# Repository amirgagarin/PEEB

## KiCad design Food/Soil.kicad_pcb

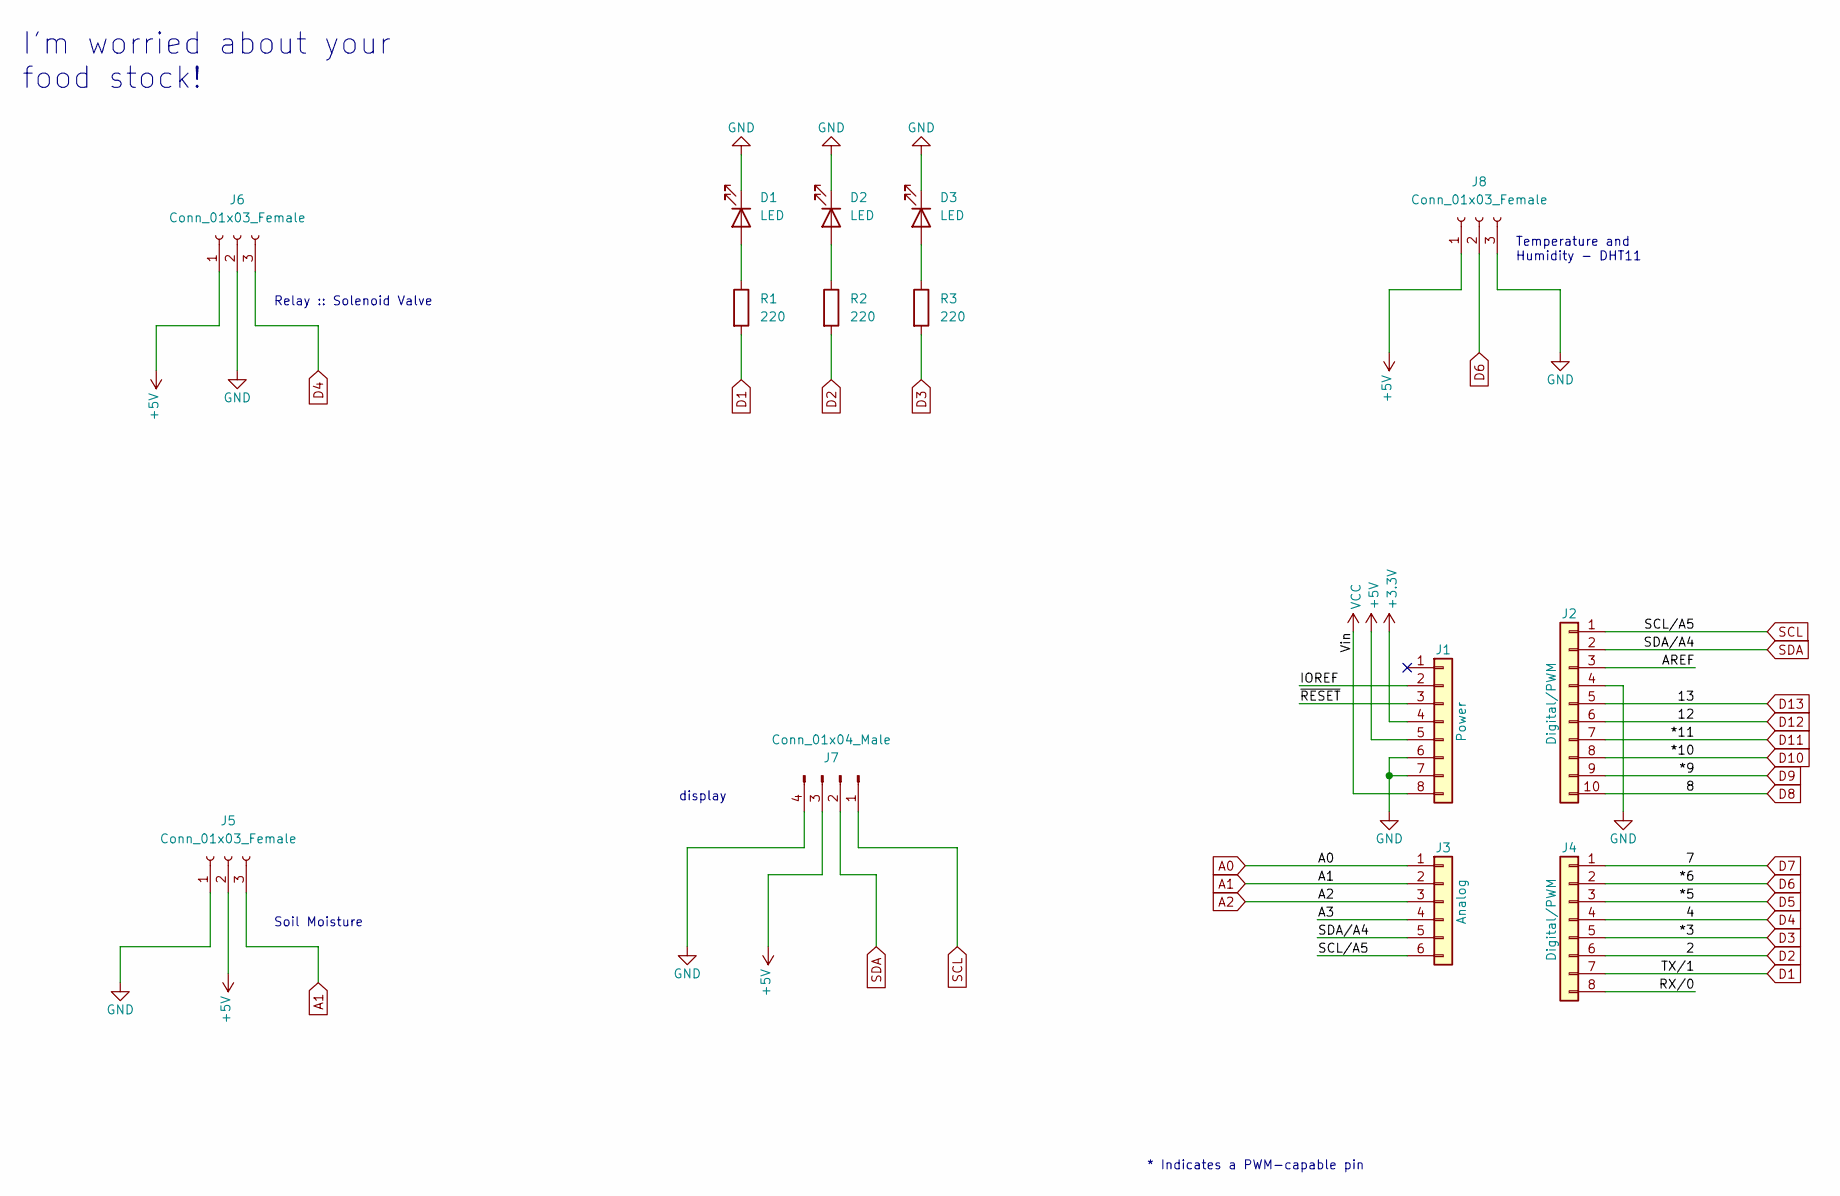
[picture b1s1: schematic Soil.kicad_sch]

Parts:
D1, D2, D3: LED; LED_D5.0mm_IRGrey
J1: Power; PinSocket_1x08_P2.54mm_Vertical
J2: Digital/PWM; PinSocket_1x10_P2.54mm_Vertical
J3: Analog; PinSocket_1x06_P2.54mm_Vertical
J4: Digital/PWM; PinSocket_1x08_P2.54mm_Vertical
J5, J8: Conn_01x03_Female; PinHeader_1x03_P2.54mm_Vertical
J6: Conn_01x03_Female; TerminalBlock_Altech_AK300-3_P5.00mm
J7: Conn_01x04_Male; PinHeader_1x04_P2.54mm_Vertical
R1, R2, R3: 220; R_Axial_DIN0207_L6.3mm_D2.5mm_P10.16mm_Horizontal

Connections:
+3V3: J1.4
+5V: J1.5, J5.2, J6.1, J7.3, J8.1
/A3: J3.4
/AREF: J2.3
/IOREF: J1.2
/RX/0: J4.8
/~RESET: J1.3
A0: J3.1
A1: J3.2, J5.3
A2: J3.3
D1: J4.7, R1.2
D2: J4.6, R2.2
D3: J4.5, R3.2
D4: J4.4, J6.3
D5: J4.3
D6: J4.2, J8.2
D7: J4.1
D8: J2.10
D9: J2.9
D10: J2.8
D11: J2.7
D12: J2.6
D13: J2.5
GND: D1.1 (K), D2.1 (K), D3.1 (K), J1.6, J1.7, J2.4, J5.1, J6.2, J7.4, J8.3
unnamed: D1.2 (A), R1.1
unnamed: D2.2 (A), R2.1
unnamed: D3.2 (A), R3.1
SCL: J2.1, J3.6, J7.1
SDA: J2.2, J3.5, J7.2
VCC: J1.8

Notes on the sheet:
display
Relay :: Solenoid Valve
Temperature and Humidity - DHT11
I'm worried about your food stock!
Soil Moisture
* Indicates a PWM-capable pin

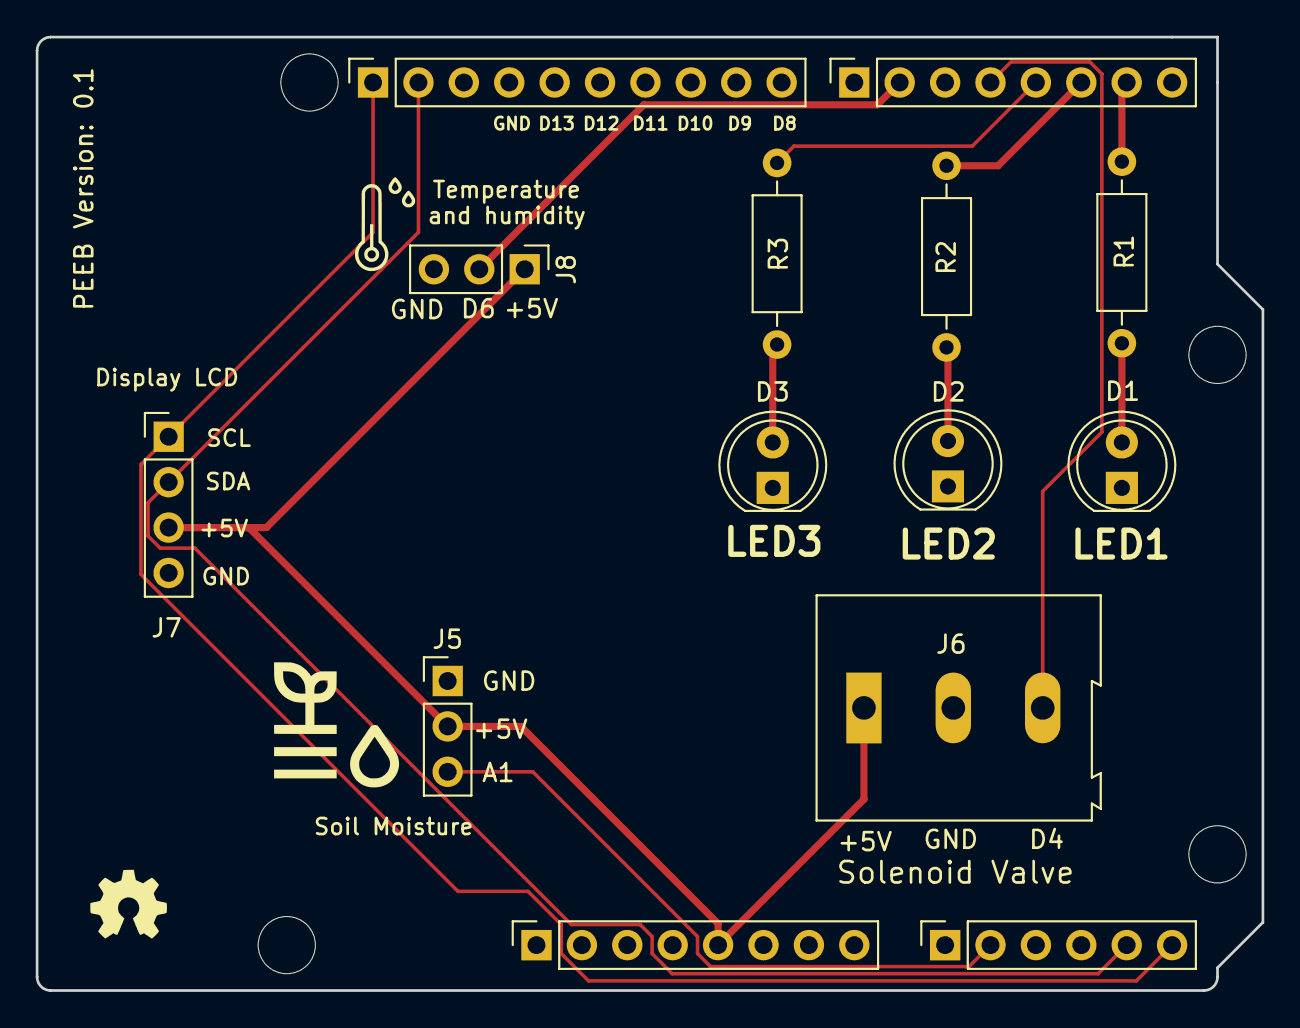
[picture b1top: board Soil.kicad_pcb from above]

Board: 2 copper layers, 68.6 x 53.3 mm, 18 parts (0 on the bottom side), 13 nets.

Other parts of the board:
MH1, MH2, MH3, MH4: MountingHole_3.2mm

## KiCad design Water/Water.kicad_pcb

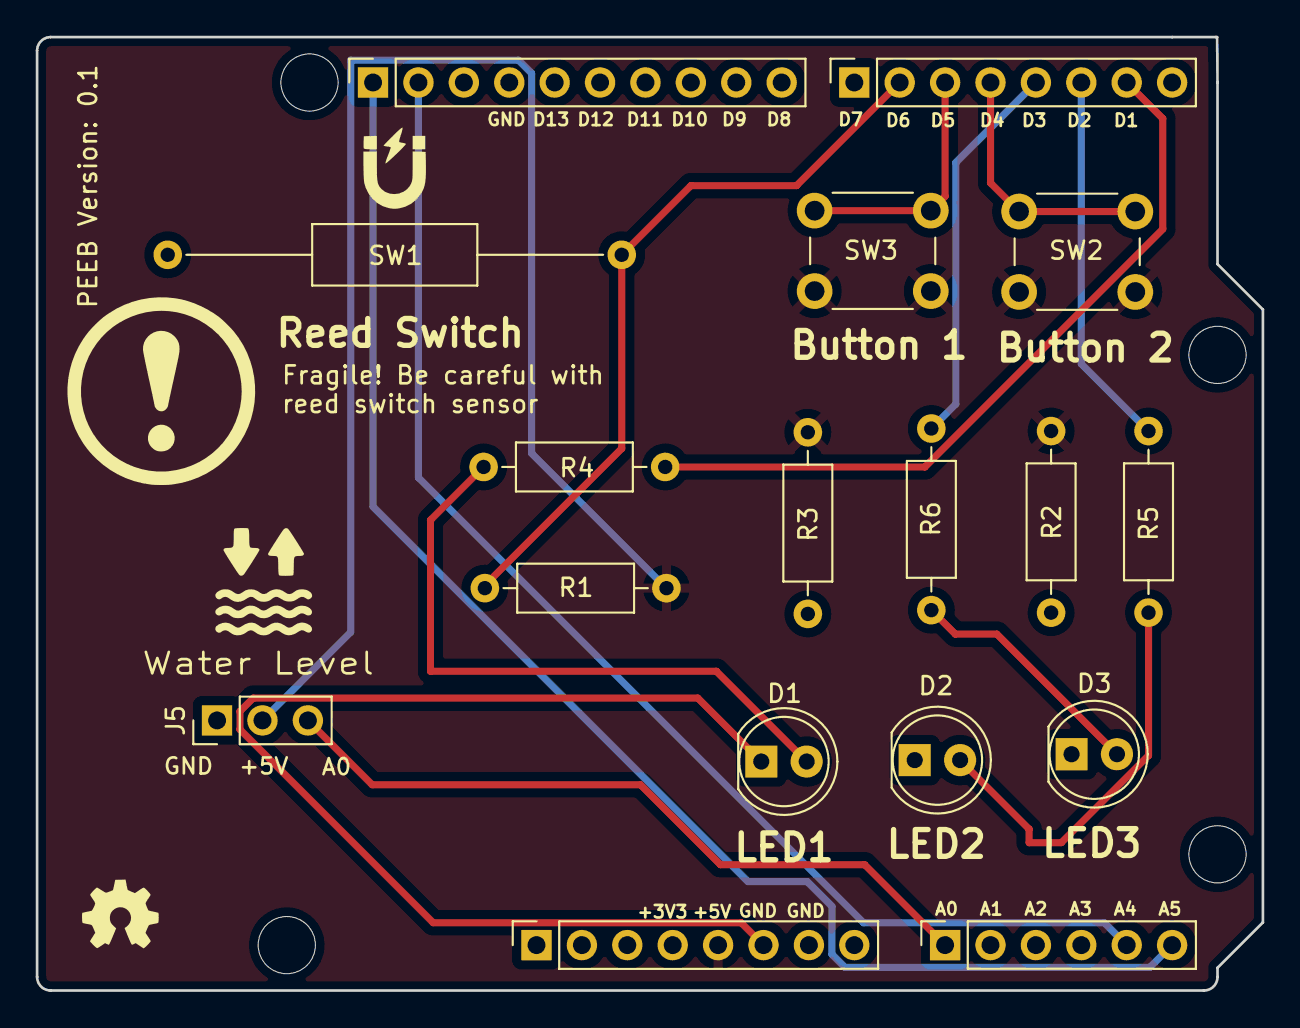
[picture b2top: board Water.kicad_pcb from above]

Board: 2 copper layers, 68.6 x 53.3 mm, 21 parts (0 on the bottom side), 14 nets.

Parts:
D1, D2, D3: LED; LED_D5.0mm_IRGrey
J1: Power; PinSocket_1x08_P2.54mm_Vertical
J2: Digital/PWM; PinSocket_1x10_P2.54mm_Vertical
J3: Analog; PinSocket_1x06_P2.54mm_Vertical
J4: Digital/PWM; PinSocket_1x08_P2.54mm_Vertical
J5: Conn_01x03_Male; PinHeader_1x03_P2.54mm_Vertical
MH1, MH2, MH3, MH4: MountingHole_3.2mm
R1: 100; R_Axial_DIN0207_L6.3mm_D2.5mm_P10.16mm_Horizontal
R2, R3: 10k; R_Axial_DIN0207_L6.3mm_D2.5mm_P10.16mm_Horizontal
R4, R5, R6: 220; R_Axial_DIN0207_L6.3mm_D2.5mm_P10.16mm_Horizontal
SW1: SW_Reed; R_Axial_DIN0309_L9.0mm_D3.2mm_P25.40mm_Horizontal
SW2, SW3: SW_Push; SW_PUSH_6mm

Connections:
+5V: J1.5, J5.2, R1.2, R2.1, R3.1, SW2.1, SW3.1
/SCL/A5: J2.1, J3.6
/SDA/A4: J2.2, J3.5
A0: J3.1, J5.3
D1: J4.7, R4.2
D2: J4.6, R5.2
D3: J4.5, R6.2
D4: J4.4, SW2.2
D5: J4.3, SW3.2
D6: J4.2, R1.1, SW1.2
GND: D1.1 (K), D2.1 (K), D3.1 (K), J1.6, J1.7, J2.4, J5.1, R2.2, R3.2, SW1.1
unnamed: D1.2 (A), R4.1
unnamed: D2.2 (A), R5.1
unnamed: D3.2 (A), R6.1

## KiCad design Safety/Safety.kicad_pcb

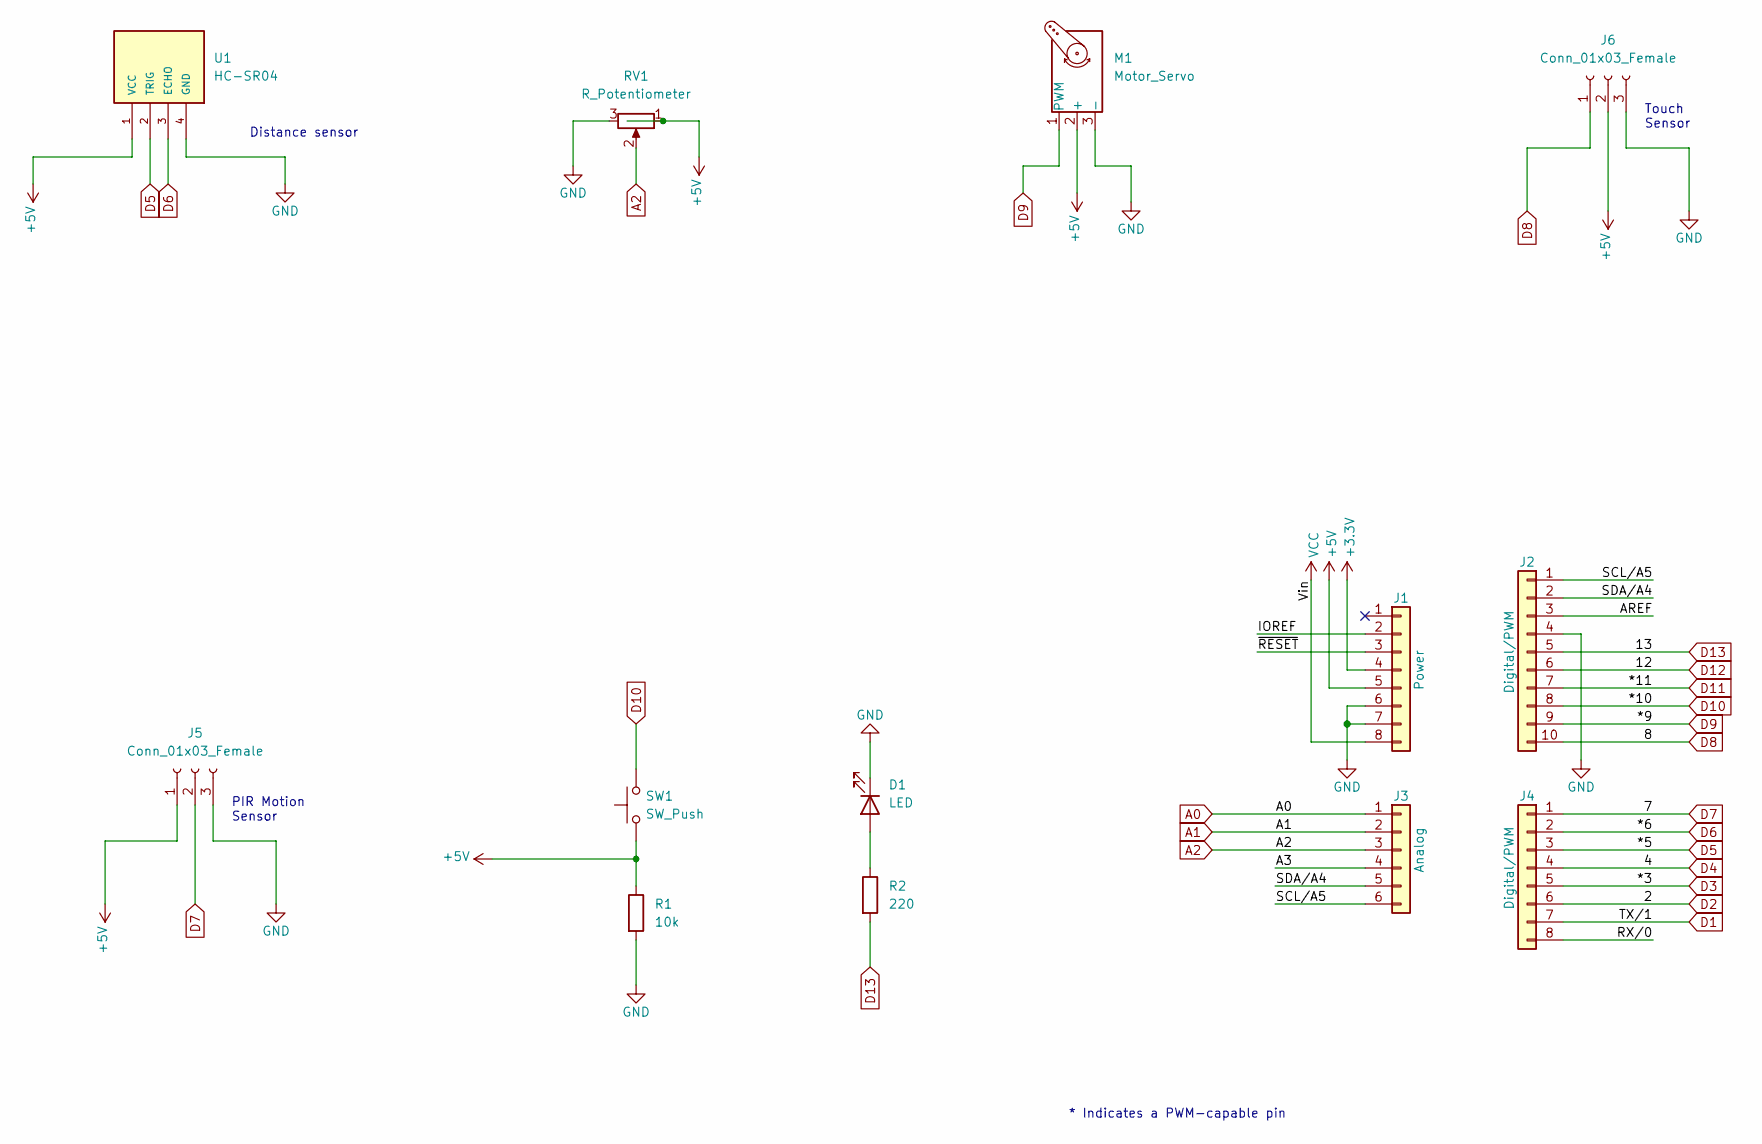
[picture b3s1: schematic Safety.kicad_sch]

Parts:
D1: LED; LED_D5.0mm_IRGrey
J1: Power; PinSocket_1x08_P2.54mm_Vertical
J2: Digital/PWM; PinSocket_1x10_P2.54mm_Vertical
J3: Analog; PinSocket_1x06_P2.54mm_Vertical
J4: Digital/PWM; PinSocket_1x08_P2.54mm_Vertical
J5, J6: Conn_01x03_Female; PinHeader_1x03_P2.54mm_Vertical
M1: Motor_Servo; PinHeader_1x03_P2.54mm_Vertical
R1: 10k; R_Axial_DIN0207_L6.3mm_D2.5mm_P10.16mm_Horizontal
R2: 220; R_Axial_DIN0207_L6.3mm_D2.5mm_P10.16mm_Horizontal
RV1: R_Potentiometer; Potentiometer_Alps_RK163_Single_Horizontal
SW1: SW_Push; SW_PUSH_6mm
U1: HC-SR04; PinHeader_1x04_P2.54mm_Vertical

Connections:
+3V3: J1.4
+5V: J1.5, J5.1, J6.2, M1.2 (+), R1.1, RV1.1, SW1.1, U1.1 (VCC)
/A3: J3.4
/AREF: J2.3
/IOREF: J1.2
/RX/0: J4.8
/SCL/A5: J2.1, J3.6
/SDA/A4: J2.2, J3.5
/~RESET: J1.3
A0: J3.1
A1: J3.2
A2: J3.3, RV1.2
D1: J4.7
D2: J4.6
D3: J4.5
D4: J4.4
D5: J4.3, U1.2 (TRIG)
D6: J4.2, U1.3 (ECHO)
D7: J4.1, J5.2
D8: J2.10, J6.1
D9: J2.9, M1.1 (PWM)
D10: J2.8, SW1.2
D11: J2.7
D12: J2.6
D13: J2.5, R2.2
GND: D1.1 (K), J1.6, J1.7, J2.4, J5.3, J6.3, M1.3 (-), R1.2, RV1.3, U1.4 (GND)
unnamed: D1.2 (A), R2.1
VCC: J1.8

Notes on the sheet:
Distance sensor
* Indicates a PWM-capable pin
Touch Sensor
PIR Motion Sensor

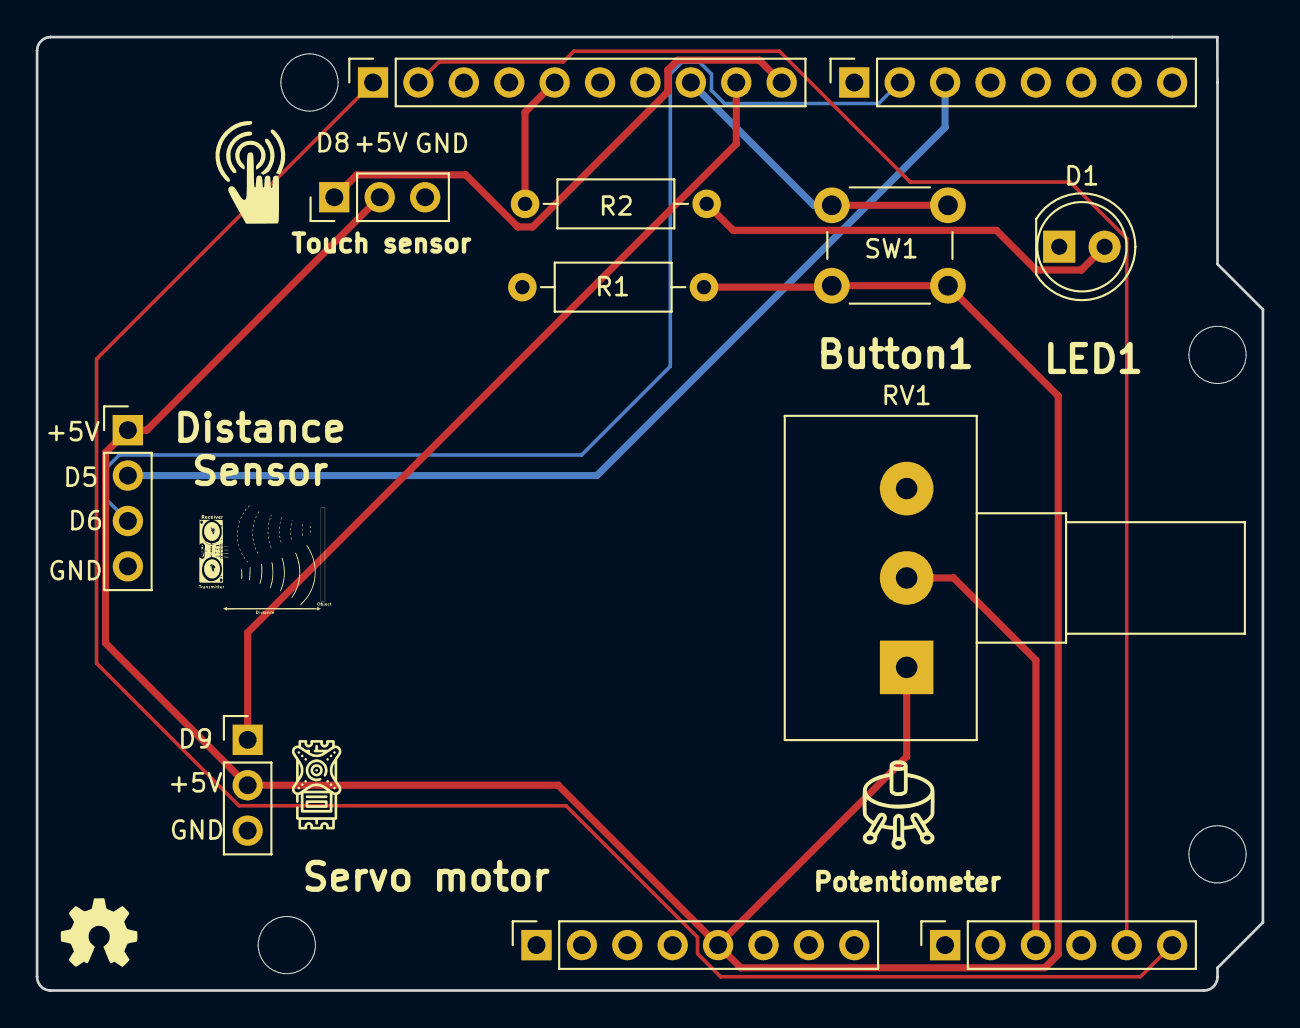
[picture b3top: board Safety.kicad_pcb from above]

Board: 2 copper layers, 68.6 x 53.3 mm, 16 parts (0 on the bottom side), 12 nets.

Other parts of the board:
MH1, MH2, MH3, MH4: MountingHole_3.2mm

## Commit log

2023-02-26 Create Generation1
2023-02-26 Initial Upload
2023-02-26 Initial Upload @ 2/2023
2023-05-04 Create LICENSE
